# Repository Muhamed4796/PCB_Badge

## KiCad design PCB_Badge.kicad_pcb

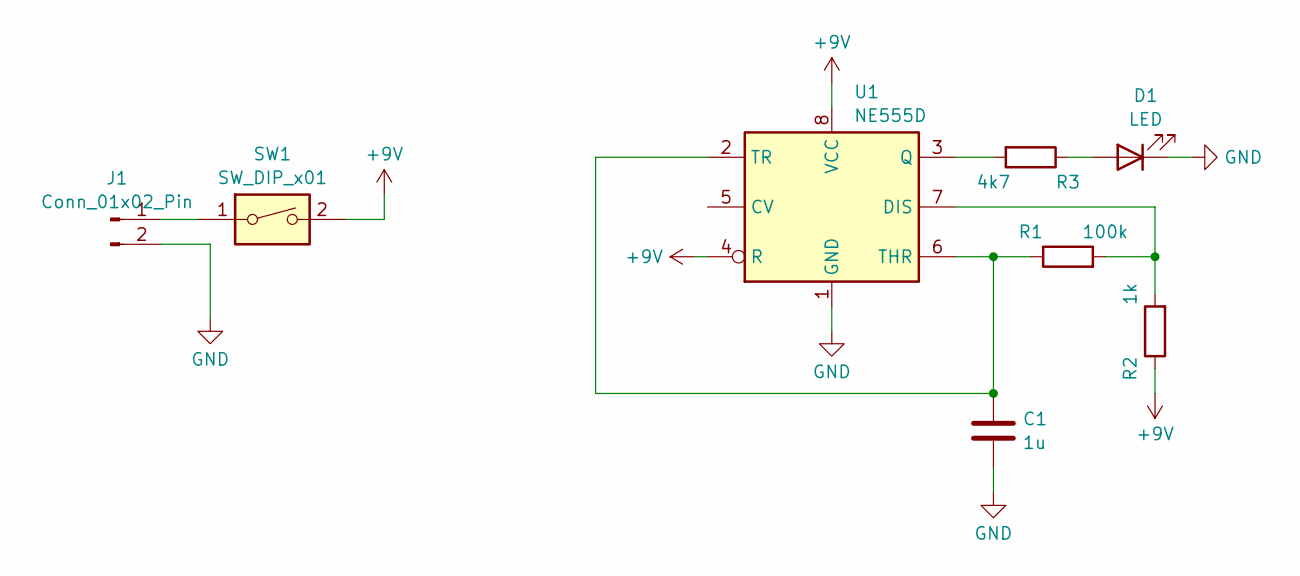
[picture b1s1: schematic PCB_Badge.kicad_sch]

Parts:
C1: 1u; C_0805_2012Metric_Pad1.18x1.45mm_HandSolder
D1: LED; LED_D4.0mm
J1: Conn_01x02_Pin; PinSocket_1x02_P2.54mm_Vertical
R1: 100k; R_0805_2012Metric_Pad1.20x1.40mm_HandSolder
R2: 1k; R_0805_2012Metric_Pad1.20x1.40mm_HandSolder
R3: 4k7; R_0805_2012Metric_Pad1.20x1.40mm_HandSolder
SW1: SW_DIP_x01; SW_DIP_SPSTx01_Slide_9.78x4.72mm_W8.61mm_P2.54mm
U1: NE555D; SOIC-8_3.9x4.9mm_P1.27mm

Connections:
+9V: R2.1, SW1.2, U1.4 (R), U1.8 (VCC)
GND: C1.2, D1.1 (K), J1.2, U1.1 (GND)
unnamed: D1.2 (A), R3.1
unnamed: J1.1, SW1.1
unnamed: R1.2, R2.2, U1.7 (DIS)
unnamed: R3.2, U1.3 (Q)
unnamed: C1.1, R1.1, U1.2 (TR), U1.6 (THR)

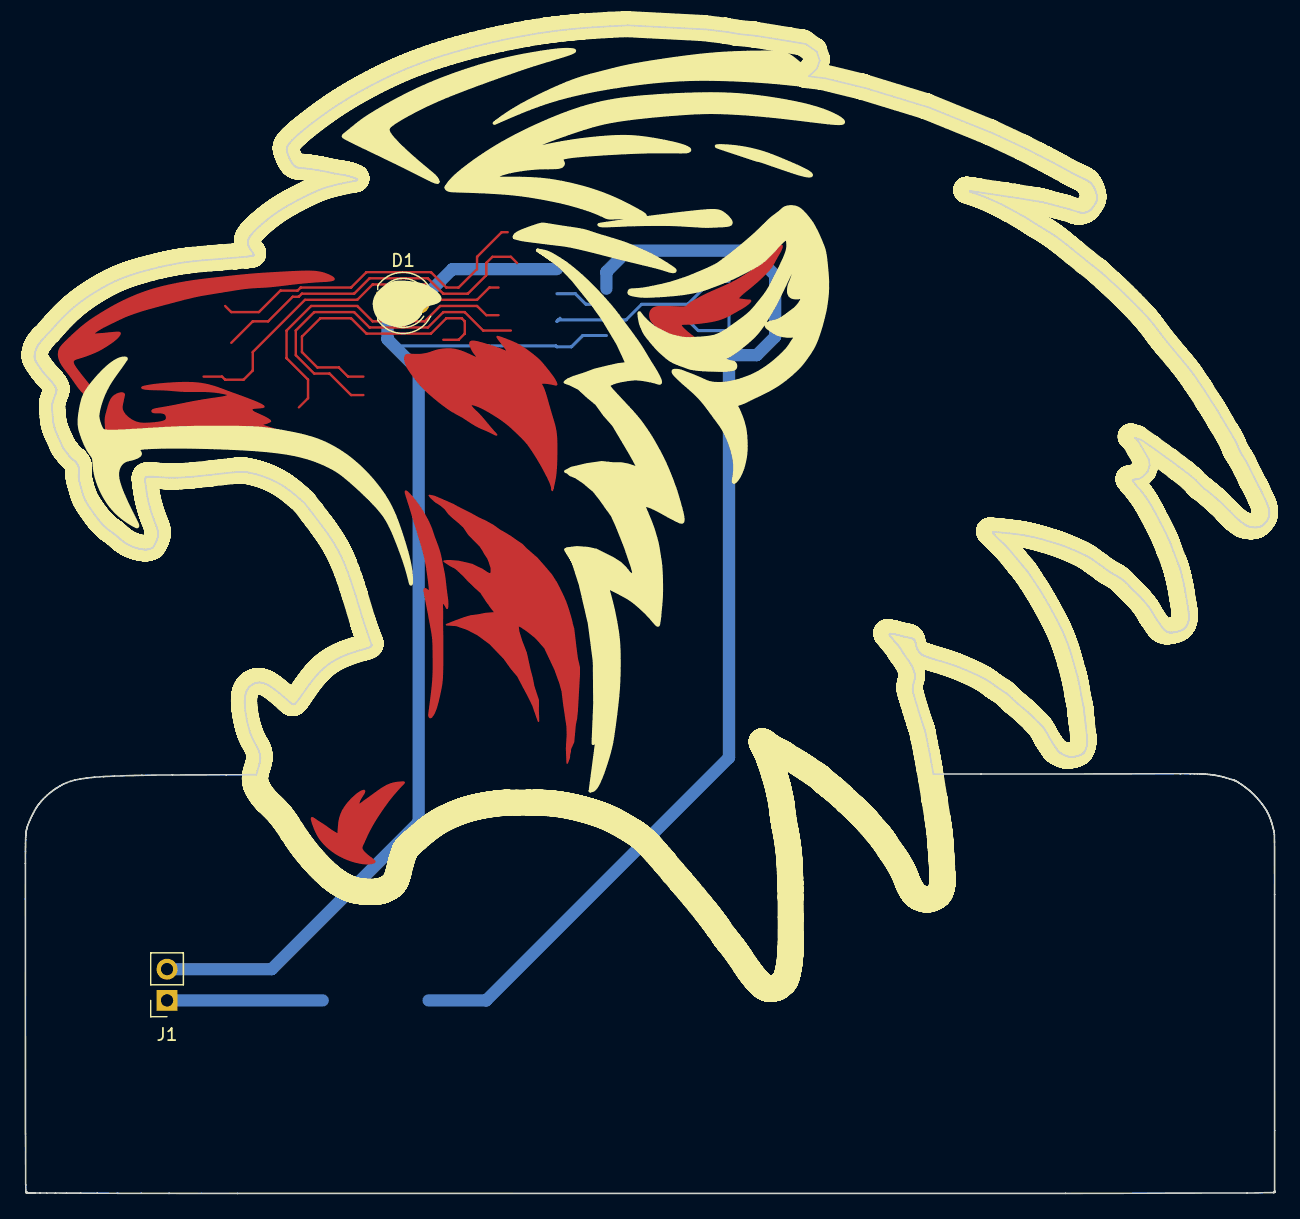
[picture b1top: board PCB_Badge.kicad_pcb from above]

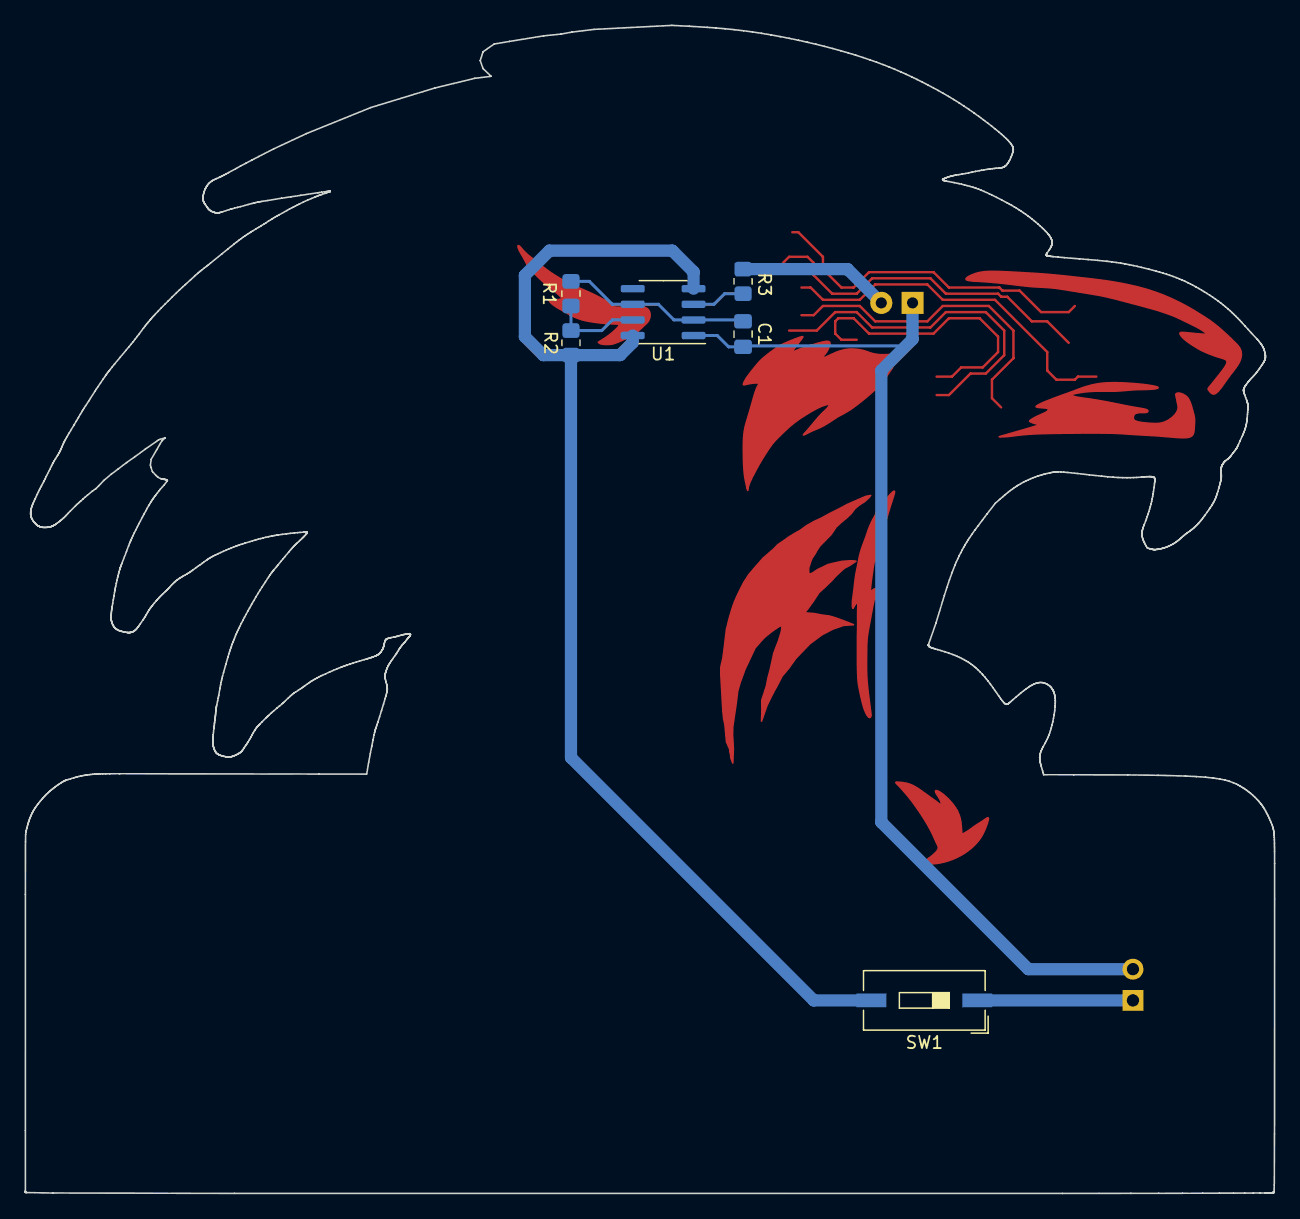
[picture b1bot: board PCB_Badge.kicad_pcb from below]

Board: 2 copper layers, 101.6 x 95.0 mm, 8 parts (6 on the bottom side), 7 nets.

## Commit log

2023-08-16 Initial push
